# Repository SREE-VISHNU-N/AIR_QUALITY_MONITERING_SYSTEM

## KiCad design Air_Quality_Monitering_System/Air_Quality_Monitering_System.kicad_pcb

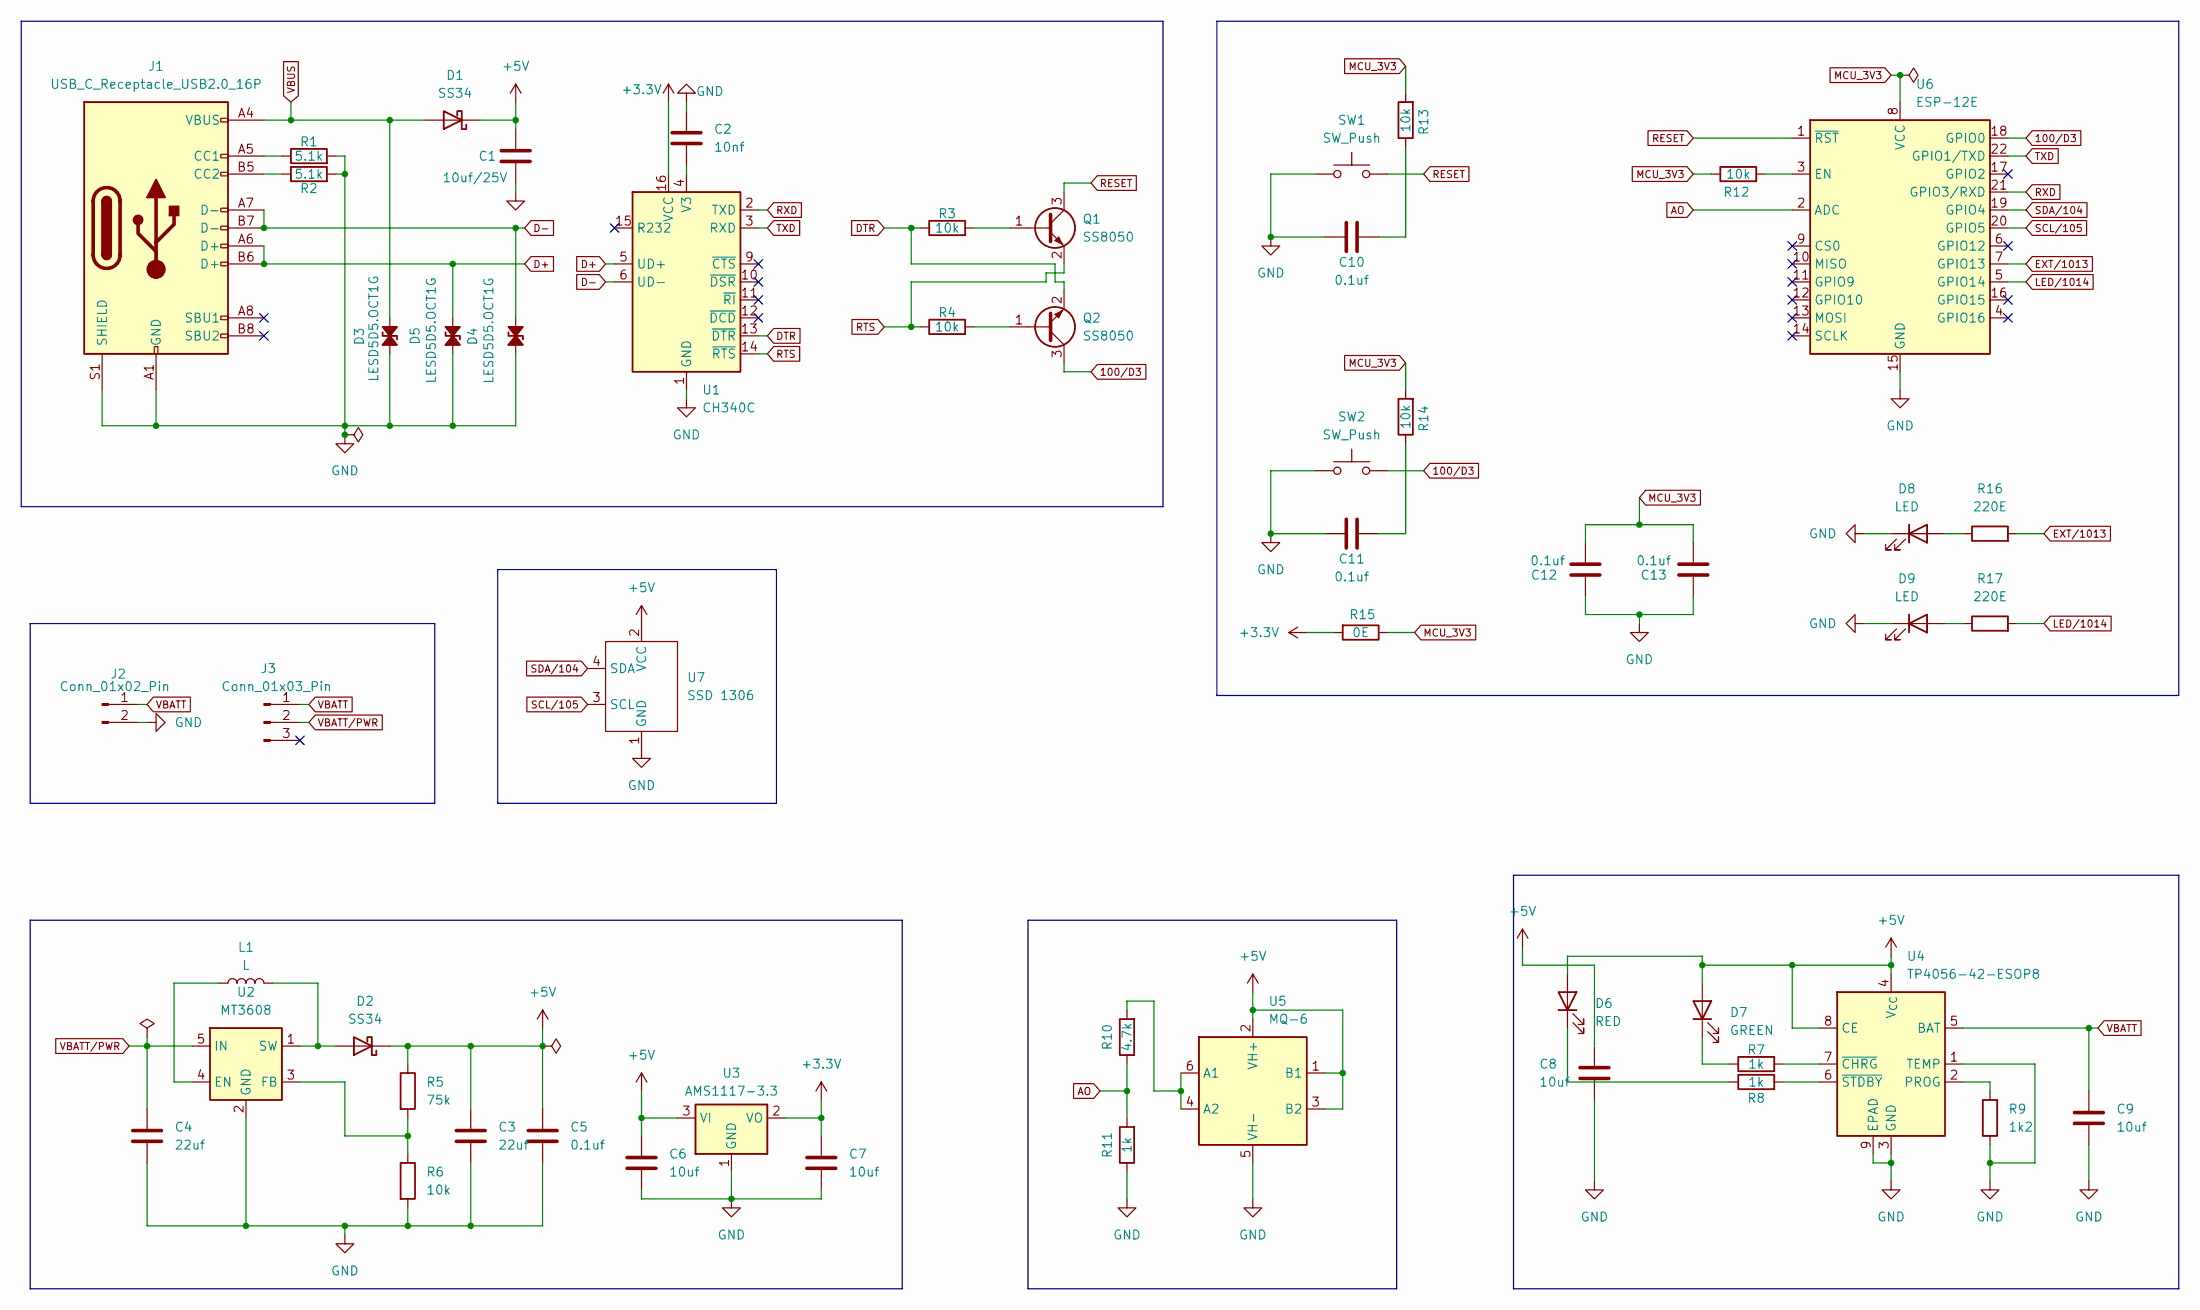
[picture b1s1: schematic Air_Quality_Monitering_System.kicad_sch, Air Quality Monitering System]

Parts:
C1: 10uf/25V; CP_Elec_6.3x5.7
C2: 10nf; C_0805_2012Metric
C3, C4: 22uf; C_0805_2012Metric
C5, C10, C11, C12, C13: 0.1uf; C_0603_1608Metric
C6, C7, C8, C9: 10uf; C_0805_2012Metric
D1, D2: SS34; D_SMA
D3, D4, D5: LESD5D5.OCT1G; D_SOD-323
D6: RED; D_0603_1608Metric
D7: GREEN; D_0603_1608Metric
D8, D9: LED; D_0603_1608Metric
J1: USB_C_Receptacle_USB2.0_16P; USB_C_Receptacle_HRO_TYPE-C-31-M-12
J2: Conn_01x02_Pin; PinHeader_1x02_P2.54mm_Vertical
J3: Conn_01x03_Pin; PinHeader_1x03_P2.54mm_Vertical
L1: L; L_6.3x6.3_H3
Q1, Q2: SS8050; SOT-23
R1, R2: 5.1k; R_0603_1608Metric
R3, R4, R6, R12, R13, R14: 10k; R_0603_1608Metric
R5: 75k; R_0603_1608Metric
R7, R8, R11: 1k; R_0603_1608Metric
R9: 1k2; R_0603_1608Metric
R10: 4.7k; R_0603_1608Metric
R15: 0E; R_0603_1608Metric
R16, R17: 220E; R_0603_1608Metric
SW1, SW2: SW_Push; SW_SPST_TL3342
U1: CH340C; SOIC-16_3.9x9.9mm_P1.27mm
U2: MT3608; SOT-23-6
U3: AMS1117-3.3; SOT-223-3_TabPin2
U4: TP4056-42-ESOP8; SOIC-8-1EP_3.9x4.9mm_P1.27mm_EP2.41x3.3mm_ThermalVias
U5: MQ-6
U6: ESP-12E
U7: SSD 1306

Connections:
100/D3: Q2.3 (C), SW2.2, U6.18 (GPIO0)
+3.3V: C7.1, R15.2, U1.16 (VCC), U3.2 (VO)
+5V: C1.1, C3.1, C5.1, C6.1, C8.1, D1.1 (K), D2.1 (K), D6.2 (A), D7.2 (A), R5.1, U3.3 (VI), U4.4 (V_{CC}), U4.8 (CE), U5.1 (B1), U5.2 (VH+), U5.3 (B2), U7.2 (VCC)
AO: R10.1, R11.2, U6.2 (ADC)
D+: D4.2 (A2), J1.A6 (D+), J1.B6 (D+), U1.5 (UD+)
D-: D5.2 (A2), J1.A7 (D-), J1.B7 (D-), U1.6 (UD-)
DTR: Q2.2 (E), R3.1, U1.13 (~DTR)
EXT/1013: R16.2, U6.7 (GPIO13)
GND: C1.2, C2.1, C3.2, C4.2, C5.2, C6.2, C7.2, C8.2, C9.2, C10.1, C11.1, C12.1, C13.2, D3.1 (A1), D4.1 (A1), D5.1 (A1), D8.1 (K), D9.1 (K), J1.A1 (GND), J1.A12 (GND), J1.B1 (GND), J1.B12 (GND), J1.S1 (SHIELD), J2.2, R1.2, R2.2, R6.2, R9.1, R11.1, SW1.1, SW2.1, U1.1 (GND), U2.2 (GND), U3.1 (GND), U4.1 (TEMP), U4.3 (GND), U4.9 (EPAD), U5.5 (VH-), U6.15 (GND), U7.1 (GND)
LED/1014: R17.2, U6.5 (GPIO14)
MCU_3V3: C12.2, C13.1, R12.1, R13.2, R14.2, R15.1, U6.8 (VCC)
unnamed: C10.2, R13.1
unnamed: C11.2, R14.1
unnamed: D2.2 (A), L1.2, U2.1 (SW)
unnamed: D6.1 (K), R8.1
unnamed: D7.1 (K), R7.1
unnamed: D8.2 (A), R16.1
unnamed: D9.2 (A), R17.1
unnamed: J1.A5 (CC1), R1.1
unnamed: J1.B5 (CC2), R2.1
unnamed: Q1.1 (B), R3.2
unnamed: Q2.1 (B), R4.2
unnamed: C2.2, U1.4 (V3)
unnamed: L1.1, U2.4 (EN)
unnamed: R5.2, R6.1, U2.3 (FB)
unnamed: R9.2, U4.2 (PROG)
unnamed: R7.2, U4.7 (~CHRG)
unnamed: R8.2, U4.6 (~STDBY)
unnamed: R10.2, U5.4 (A2), U5.6 (A1)
unnamed: R12.2, U6.3 (EN)
RESET: Q1.3 (C), SW1.2, U6.1 (~RST)
RTS: Q1.2 (E), R4.1, U1.14 (~RTS)
RXD: U1.2 (TXD), U6.21 (GPIO3/RXD)
SCL/105: U6.20 (GPIO5), U7.3 (SCL)
SDA/104: U6.19 (GPIO4), U7.4 (SDA)
TXD: U1.3 (RXD), U6.22 (GPIO1/TXD)
VBATT: C9.1, J2.1, J3.1, U4.5 (BAT)
VBATT/PWR: C4.1, J3.2, U2.5 (IN)
VBUS: D1.2 (A), D3.2 (A2), J1.A4 (VBUS), J1.A9 (VBUS), J1.B4 (VBUS), J1.B9 (VBUS)

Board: 4 copper layers, 54 parts (0 on the bottom side), 39 nets, no tracks yet.

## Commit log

2025-03-30 Project Folder Added
2025-03-30 TEST
2025-03-30 Test one is completed
2025-03-30 Ready to Project
2025-03-30 Project started now
2025-03-30 Schematics are finished
2025-03-31 Footprints are assigned
2025-04-09 PCB design was started
